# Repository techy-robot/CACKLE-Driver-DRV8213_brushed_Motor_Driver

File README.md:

---
modified: 2025-11-07T22:06:51-07:00
---

# DRV8213 brushed Motor Driver

> [!TIP]
> This board is part of a larger modular control board ecosystem, [CACKLE](https://github.com/techy-robot/CACKLE)

This is a single motor driver based on the DRV8213RTER Texas Instruments chip. It is capable of 4 amps current in a voltage range of 1.65 to 11 volts. This is basically a 2-pin H-bridge driver with integrated protection logic. Driving one pin with PWM will cause the motor to go in one direction, driving both pins will cause braking, and disabling both pins will enable coasting.

The chip has one current sense output, which is tied to both ADC pins A and B on the driver module. Pin C of the ADC pins is tied to FAULT, which is pulled low on triggering.  Motor control inputs are on Pins A and B, and the motor output is through a JST PH (2mm Pitch) 2-pin connector which matches the same pin order as the input. The JST-PH connector is 5mm high and is positioned near the center of the board.

The module is a 4-layer PCB with additional exposed traces for the power and ground to add solder for more current carrying capability. I designed it to carry 10 amps with 1 oz outer copper and 0.5oz inner copper, which can be increased to 20 amps current by adding solder. This was the cheapest method to go with, since 2 oz copper would add an additional 30$ per 5 boards. 

3D model:

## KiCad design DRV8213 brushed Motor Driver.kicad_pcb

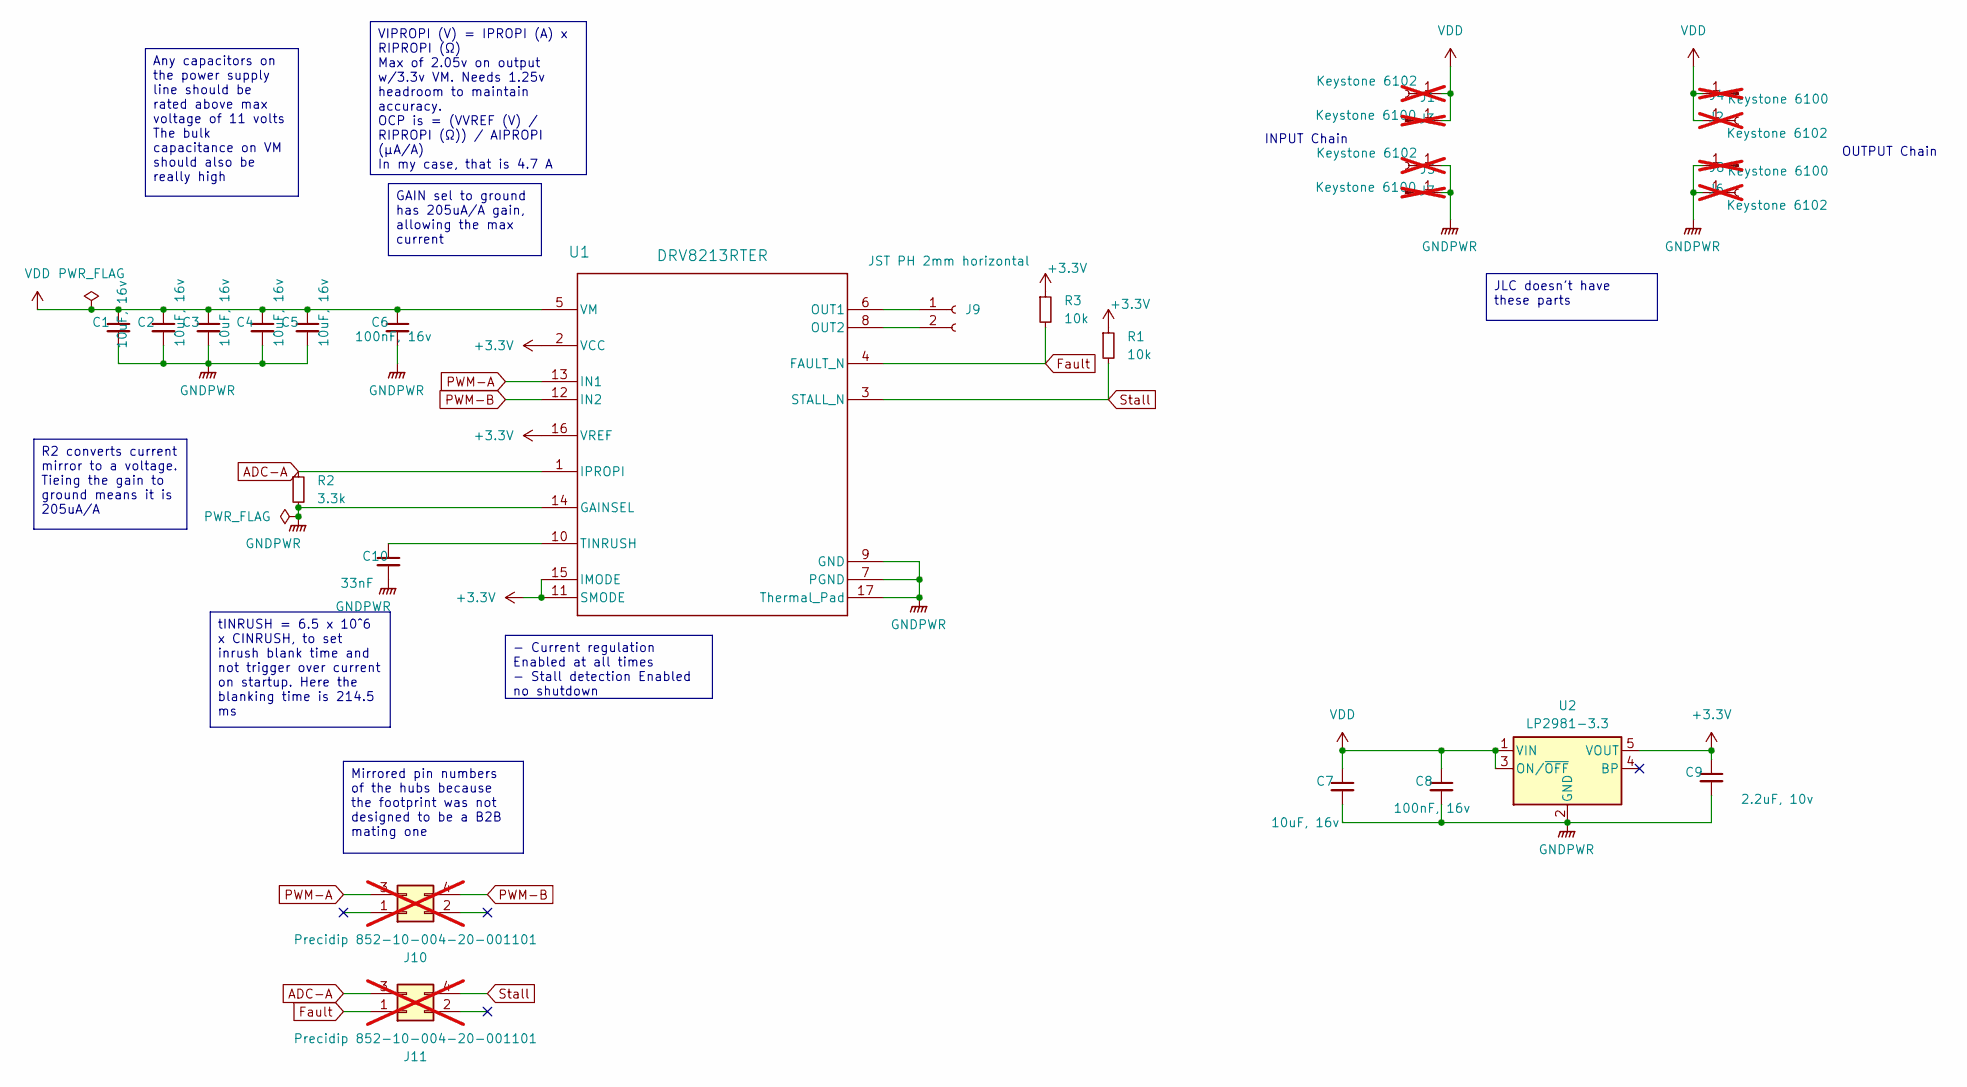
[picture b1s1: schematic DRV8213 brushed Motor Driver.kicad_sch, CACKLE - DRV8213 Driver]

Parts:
C1, C2, C3, C4, C5, C7: 10uF, 16v; C_0603_1608Metric; LCSC C96446
C6, C8: 100nF, 16v; C_0402_1005Metric; LCSC C1525
C9: 2.2uF, 10v; C_0402_1005Metric; LCSC C12530
C10: 33nF; C_0603_1608Metric; LCSC C21117
J1, J2, J5, J6: Keystone 6102; Keystone_6102; not fitted
J3, J4, J7, J8: Keystone 6100; Keystone_6100; not fitted
J9: JST PH 2mm horizontal; JST_PH_S2B-PH-K_1x02_P2.00mm_Horizontal; LCSC C160237
J10, J11: Precidip 852-10-004-20-001101; not fitted
R1, R3: 10k; R_0402_1005Metric; LCSC C25744
R2: 3.3k; R_0402_1005Metric; LCSC C25890
U1: DRV8213RTER; WQFN-16-1EP_3x3mm_P0.5mm_EP1.68x1.68mm_ThermalVias
U2: LP2981-3.3; SOT-23-5; LCSC C129997

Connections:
+3.3V: C9.1, R1.1, R3.1, U1.2 (VCC), U1.11 (SMODE), U1.15 (IMODE), U1.16 (VREF), U2.5 (VOUT)
ADC-A: J11.3, R2.1, U1.1 (IPROPI)
Fault: J11.1, R3.2, U1.4 (FAULT_N)
GNDPWR: C1.2, C2.2, C3.2, C4.2, C5.2, C6.2, C7.2, C8.2, C9.2, C10.2, J5.1, J6.1, J7.1, J8.1, R2.2, U1.7 (PGND), U1.9 (GND), U1.14 (GAINSEL), U1.17 (Thermal_Pad), U2.2 (GND)
unnamed: J9.1, U1.6 (OUT1)
unnamed: J9.2, U1.8 (OUT2)
unnamed: C10.1, U1.10 (TINRUSH)
PWM-A: J10.3, U1.13 (IN1)
PWM-B: J10.4, U1.12 (IN2)
Stall: J11.4, R1.2, U1.3 (STALL_N)
VDD: C1.1, C2.1, C3.1, C4.1, C5.1, C6.1, C7.1, C8.1, J1.1, J2.1, J3.1, J4.1, U1.5 (VM), U2.1 (VIN), U2.3 (ON/~OFF)

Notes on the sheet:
INPUT Chain
OUTPUT Chain
GAIN sel to ground has 205uA/A gain, allowing the max current
R2 converts current mirror to a voltage. Tieing the gain to ground means it is 205uA/A
VIPROPI (V) = IPROPI (A) x RIPROPI (Ω) Max of 2.05v on output w/3.3v VM. Needs 1.25v headroom to maintain accuracy. OCP is = (VVREF (V) / RIPROPI (Ω)) / AIPROPI (μA/A) In my case, that is 4.7 A
Mirrored pin numbers of the hubs because the footprint was not designed to be a B2B mating one
- Current regulation Enabled at all times - Stall detection Enabled no shutdown
JLC doesn't have these parts
Any capacitors on the power supply line should be rated above max voltage of 11 volts The bulk capacitance on VM should also be really high
tINRUSH = 6.5 x 10^6 x CINRUSH, to set inrush blank time and not trigger over current on startup. Here the blanking time is 214.5 ms

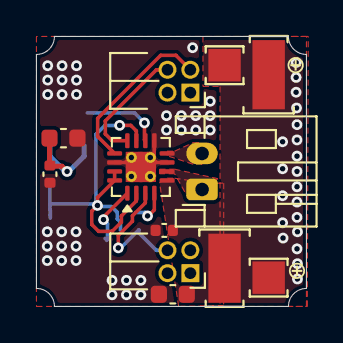
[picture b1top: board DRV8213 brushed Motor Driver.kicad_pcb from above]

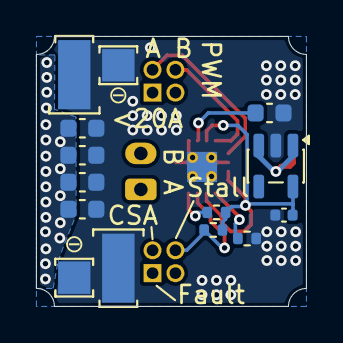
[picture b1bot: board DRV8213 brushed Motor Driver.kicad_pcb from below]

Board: 4 copper layers, 15.0 x 15.0 mm, 26 parts (14 on the bottom side), 11 nets.

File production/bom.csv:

Designator,Footprint,Quantity,Value,LCSC Part #
"C1, C2, C3, C4, C5, C7",0603,6,"10uF, 16v",C96446
C10,0603,1,33nF,C21117
"C6, C8",0402,2,"100nF, 16v",C1525
C9,0402,1,"2.2uF, 10v",C12530
"J1, J2, J5, J6",Keystone_6102,4,Keystone 6102,
"J10, J11",Precidip 852-10-004-20-001101,2,Precidip 852-10-004-20-001101,
"J3, J4, J7, J8",Keystone_6100,4,Keystone 6100,
J9,JST_PH_S2B-PH-K_1x02_P2.00mm_Horizontal,1,JST PH 2mm horizontal,C160237
"R1, R3",0402,2,10k,C25744
R2,0402,1,3.3k,C25890
U1,WQFN-16-1EP_3x3mm_P0.5mm_EP1.68x1.68mm_ThermalVias,1,DRV8213RTER,
U2,SOT-23-5,1,LP2981-3.3,C129997

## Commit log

2024-12-31 Rearranged design files
    Instead of "Kicad" the main design folder is now named "Hardware" since I have gerbers and notes besides the kicad files. I have also put my designs in their proper categories.
2025-01-01 Updated files for JLC DFM checks
2025-01-02 Added schematic PDFs for all boards
2025-01-04 Added gerber zip files
2025-01-13 Added README files for each module
2025-01-13 Changed link names for schematic embeds not displayin
    In Obsidian I can see the pdf embeds perfectly fine, but Github doesn't want to show embedded PDFs. I changed the link alias to "Schematic PDF" so people know what the link is when it doesn't display
2025-03-19 Added pictures to each module
    Next I need to add readmes for each!
2025-10-10 Moved all current production files to Proto 1.
    I haven't made a 2nd prototype yet
2025-11-07 Added License
2025-11-08 Moved stencil jig from monorepo to here
2025-11-08 Updated README with link to main repo
2025-11-10 Added gitignore
2025-11-15 Updated connector parts in schematic
2025-11-15 Switched out and arranged new connectors
2025-11-15 Updated date and version
2025-11-15 Split Stall and Fault detection
2025-11-15 Clarified 3v3 regulator and caps
2025-11-15 Added inrush current blank capacitor
2025-11-15 Update ADC pin assignment
2025-11-15 Relayout with new components
2025-11-15 Finished reroute
2025-11-15 Hide reference values on silkscreen
2025-11-15 Reversed connector pin assignments to mirror hub
    Technically any pin would work, but I want it logical order with A matching with A. Some hubs may not have enough pins also, so most important pins go first. I might change the footprint numbers to m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
2025-11-15 Fixed Silkscreen
2025-11-15 Tweaked silkscreen and via placement
2025-11-15 Clarified expected voltage range based on datasheet, updated mask
2025-11-15 Removed 3v3 test pad
2025-11-16 Fixed connector placement
    It was overlapping a whole millimeter!
2025-11-16 Fabrication outputs
2025-11-16 Updated media
2025-11-17 Add 1mm round corner cutouts to every edge
    This is a future proofing step for an idea I had, it may not come to anything, but whatever
2025-11-18 Fixed connector alignment
2025-11-18 Fixed critical error

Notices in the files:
DRV8213 brushed Motor Driver.kicad_pcb:
Licensed under CERN-OHL-S V2
